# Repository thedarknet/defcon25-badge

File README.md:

# defcon25-badge
Badge Related items for defcon 25

Assembly instructions are located here:

https://dcdark.net/2017/badge/index.html

-----
Installation of IDE:
Follow the following instructions (step by step):  

http://gnuarmeclipse.github.io/install/

	Notes: on Window's have gotten both Mars and Luna to work
	on linux i've only gotten luna to work (on ubuntu 16.04 LTS)

Once eclipse is set up here's what the debug config needs to look like, notes the 2 -f openocd scripts that must be configured.

For 2017 development we are using this nucleo board, while it is not the exact MCU we plan to use it is close and the one we want to use does not have a dev kit.

http://www.st.com/content/st_com/en/products/evaluation-tools/product-evaluation-tools/mcu-eval-tools/stm32-mcu-eval-tools/stm32-mcu-nucleo/nucleo-f302r8.html

If you have the actual badge board you'll need debugging to look like this:

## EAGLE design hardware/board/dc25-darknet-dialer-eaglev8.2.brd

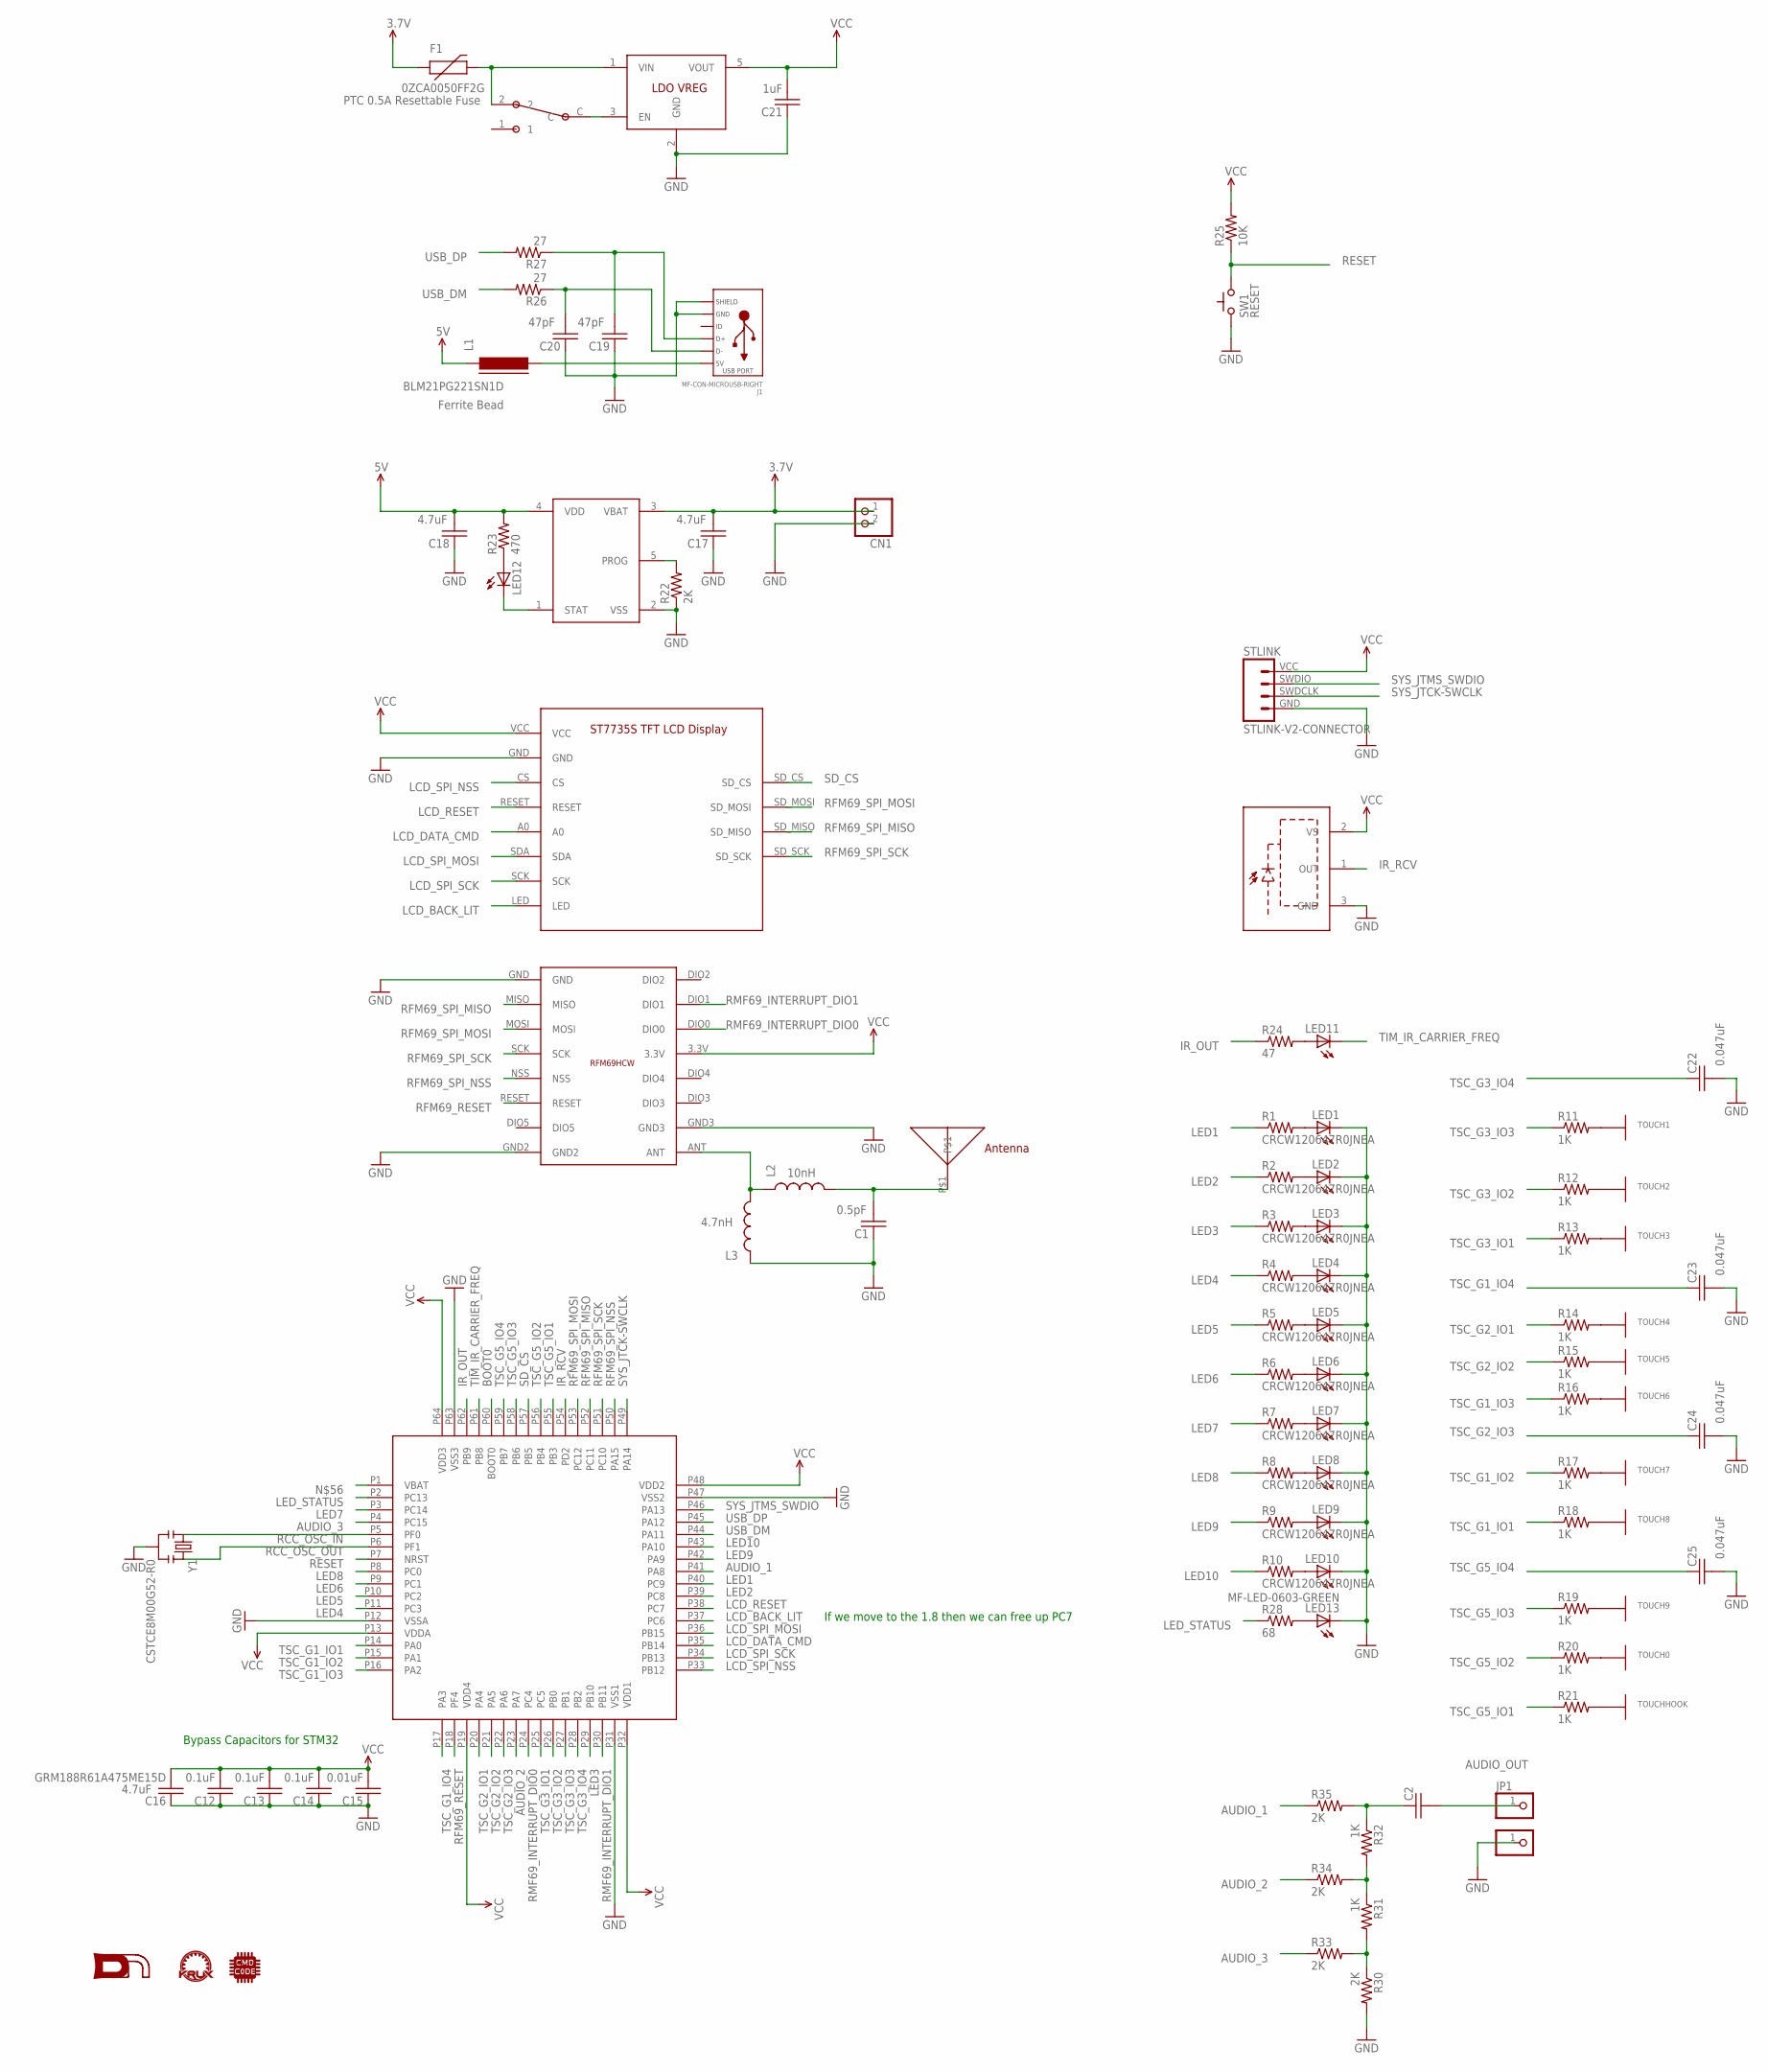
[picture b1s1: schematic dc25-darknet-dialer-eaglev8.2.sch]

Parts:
C1: 251R14S0R5BV4T; C0603
C2: GRM188C80G106ME47D; C0603
C12, C13, C14: 0.1uF; C0603
C15: 0.01uF; C0603
C16, C17, C18: GRM188R61A475ME15D; C0603
C19, C20: C0603C470J3GACTU; C0603
C21: 1uF; C0603
C22, C23, C24, C25: C0603C473J3RACAUTO; C0603
CN1: JST_2PIN-THM-RA; JST-PH-2-THM-RA
F1: 0ZCA0050FF2G; PTC-1206
J1: MF-CON-MICROUSB-RIGHT; MICROUSB-RIGHT
JP1, JP2: PINHD-1X1CB; 1X01-CLEANBIG
L1: BLM21PG221SN1D; FB603
L2: CI160808-10NJ; 0603
L3: CI160808-4N7D; 0603
LED1, LED2, LED3, LED4, LED5, LED6, LED7, LED8, LED9, LED10: LEDREVERSEMOUNT_NOPASTE; GULLWING_LED_NOPASTE
LED11: LED5MM
LED12, LED13: MF-LED-0603-GREEN; LED-0603
R1, R2, R3, R4, R5, R6, R7, R8, R9, R10: CRCW120647R0JNEA; 1206
R11, R12, R13, R14, R15, R16, R17, R18, R19, R20, R21, R31, R32: 1K; 0603-RES
R22, R30, R33, R34, R35: 2K; 0603-RES
R23: 470; 0603-RES
R24: 47; 0207/7
R25: 10K; 0603-RES
R26, R27: 27; 0603-RES
R28: 68; 0603-RES
STLINK: STLINK-V2-CONNECTOR; 1X04
SW1: RESET; TACTILE-2PIN-NARROW
TOUCH0: CAP_TOUCH0; CAP_TOUCH_PAD_0
TOUCH1: CAP_TOUCH1; CAP_TOUCH_PAD_1
TOUCH2: CAP_TOUCH2; CAP_TOUCH_PAD_2
TOUCH3: CAP_TOUCH3; CAP_TOUCH_PAD_3
TOUCH4: CAP_TOUCH4; CAP_TOUCH_PAD_4
TOUCH5: CAP_TOUCH5; CAP_TOUCH_PAD_5
TOUCH6: CAP_TOUCH6; CAP_TOUCH_PAD_6
TOUCH7: CAP_TOUCH7; CAP_TOUCH_PAD_7
TOUCH8: CAP_TOUCH8; CAP_TOUCH_PAD_8
TOUCH9: CAP_TOUCH9; CAP_TOUCH_PAD_9
TOUCHHOOK: CAP_TOUCHHOOK; CAP_TOUCH_PAD_HOOK
U1: BU33SD5WG-TR; SOT23-5
U2: MCP73831T-5ACI/OT; SOT23-5
U3: SOP22FLAT; IR-MODULE_FLAT
U$1: DN_LOGODC25; DARKNET_LOGO_DC25
U$2: STM32F302RBT6; LQFP64
U$11: SWITCH_SPDT; SPDT_SSAJ120100
U$12: KRUX_LOGO
U$15: RFM69HCWRFM69HCWSMDNOPASTE; 16PIN-PCB-SMD-NOPASTE
U$21: 0915AT43A0026E; CHIP_ANTENNA_1.8X8MM
U$22: ST7735S_LCD_MODULE; ST7735S_LCD_DISPLAY
U$23: CMD_C0DE_LOGO
Y1: CSTCE8M00G52-R0; RESONATOR-SMD

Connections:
ANT: L2.1, L3.2, U$15.ANT
AUDIO_1: R35.1, U$2.P41 (PA8)
AUDIO_2: R34.1, U$2.P23 (PA7)
AUDIO_3: R33.1, U$2.P4 (PC15)
AUDIO_OUT: C2.2, JP1.1
BOOT0: U$2.P60 (BOOT0)
GND: C1.1, C12.1, C13.1, C14.1, C15.1, C16.1, C17.1, C18.1, C19.1, C20.1, C21.1, C22.2, C23.2, C24.2, C25.2, CN1.2 (1), J1.5 (GND), J1.S1 (SLD), J1.S2 (SLD), J1.S3 (SLD), J1.S4 (SLD), J1.S5 (SLD), J1.S6 (SLD), JP2.1, L3.1, LED1.C, LED2.C, LED3.C, LED4.C, LED5.C, LED6.C, LED7.C, LED8.C, LED9.C, LED10.C, LED13.C, R22.1, R30.2, STLINK.GND, SW1.P$2 (C), U1.2 (GND), U2.2 (VSS), U3.3 (GND), U$2.P12 (VSSA), U$2.P31 (VSS1), U$2.P47 (VSS2), U$2.P63 (VSS3), U$15.GND, U$15.GND2, U$15.GND3, U$22.GND, Y1.2
IR_OUT: R24.1, U$2.P62 (PB9)
IR_RCV: U3.1 (OUT), U$2.P54 (PD2)
LCD_BACK_LIT: U$2.P37 (PC6), U$22.LED
LCD_DATA_CMD: U$2.P35 (PB14), U$22.A0
LCD_RESET: U$2.P38 (PC7), U$22.RESET
LCD_SPI_MOSI: U$2.P36 (PB15), U$22.SDA
LCD_SPI_NSS: U$2.P33 (PB12), U$22.CS
LCD_SPI_SCK: U$2.P34 (PB13), U$22.SCK
LED1: R1.1, U$2.P40 (PC9)
LED2: R2.1, U$2.P39 (PC8)
LED3: R3.1, U$2.P29 (PB10)
LED4: R4.1, U$2.P11 (PC3)
LED5: R5.1, U$2.P10 (PC2)
LED6: R6.1, U$2.P9 (PC1)
LED7: R7.1, U$2.P3 (PC14)
LED8: R8.1, U$2.P8 (PC0)
LED9: R9.1, U$2.P42 (PA9)
LED10: R10.1, U$2.P43 (PA10)
LED_STATUS: R28.1, U$2.P2 (PC13)
unnamed: R11.2, TOUCH1.PAD
unnamed: R12.2, TOUCH2.PAD
unnamed: R13.2, TOUCH3.PAD
unnamed: R14.2, TOUCH4.PAD
unnamed: R15.2, TOUCH5.PAD
unnamed: R16.2, TOUCH6.PAD
unnamed: R17.2, TOUCH7.PAD
unnamed: R18.2, TOUCH8.PAD
unnamed: R19.2, TOUCH9.PAD
unnamed: R20.2, TOUCH0.PAD
unnamed: R21.2, TOUCHHOOK.P$1
unnamed: LED1.A, R1.2
unnamed: LED2.A, R2.2
unnamed: LED3.A, R3.2
unnamed: LED4.A, R4.2
unnamed: LED5.A, R5.2
unnamed: LED6.A, R6.2
unnamed: LED7.A, R7.2
unnamed: LED8.A, R8.2
unnamed: LED9.A, R9.2
unnamed: LED10.A, R10.2
unnamed: R22.2, U2.5 (PROG)
unnamed: LED11.A, R24.2
unnamed: LED12.A, R23.1
unnamed: LED12.C, U2.1 (STAT)
unnamed: C19.2, J1.3 (D+), R27.1
unnamed: C20.2, J1.2 (D-), R26.1
unnamed: J1.1 (5V), L1.2
unnamed: LED13.A, R28.2
unnamed: F1.2, U1.1 (VIN), U$11.2
unnamed: C1.2, L2.2, U$21.P$1
unnamed: U1.3 (EN), U$11.C
unnamed: C2.1, R32.1, R35.2
unnamed: R31.1, R32.2, R34.2
unnamed: R30.1, R31.2, R33.2
RCC_OSC_IN: U$2.P5 (PF0), Y1.1
RCC_OSC_OUT: U$2.P6 (PF1), Y1.3
RESET: R25.1, SW1.P$1 (A), U$2.P7 (NRST)
RFM69_RESET: U$2.P18 (PF4), U$15.RESET
RFM69_SPI_MISO: U$2.P52 (PC11), U$15.MISO, U$22.SD_MISO
RFM69_SPI_MOSI: U$2.P53 (PC12), U$15.MOSI, U$22.SD_MOSI
RFM69_SPI_NSS: U$2.P50 (PA15), U$15.NSS
RFM69_SPI_SCK: U$2.P51 (PC10), U$15.SCK, U$22.SD_SCK
RMF69_INTERRUPT_DIO0: U$2.P24 (PC4), U$15.DIO0
RMF69_INTERRUPT_DIO1: U$2.P30 (PB11), U$15.DIO1
SD_CS: U$2.P57 (PB5), U$22.SD_CS
SYS_JTCK-SWCLK: STLINK.SWDCLK, U$2.P49 (PA14)
SYS_JTMS_SWDIO: STLINK.SWDIO, U$2.P46 (PA13)
TIM_IR_CARRIER_FREQ: LED11.K (C), U$2.P61 (PB8)
TSC_G1_IO1: R18.1, U$2.P14 (PA0)
TSC_G1_IO2: R17.1, U$2.P15 (PA1)
TSC_G1_IO3: R16.1, U$2.P16 (PA2)
TSC_G1_IO4: C23.1, U$2.P17 (PA3)
TSC_G2_IO1: R14.1, U$2.P20 (PA4)
TSC_G2_IO2: R15.1, U$2.P21 (PA5)
TSC_G2_IO3: C24.1, U$2.P22 (PA6)
TSC_G3_IO1: R13.1, U$2.P25 (PC5)
TSC_G3_IO2: R12.1, U$2.P26 (PB0)
TSC_G3_IO3: R11.1, U$2.P27 (PB1)
TSC_G3_IO4: C22.1, U$2.P28 (PB2)
TSC_G5_IO1: R21.1, U$2.P55 (PB3)
TSC_G5_IO2: R20.1, U$2.P56 (PB4)
TSC_G5_IO3: R19.1, U$2.P58 (PB6)
TSC_G5_IO4: C25.1, U$2.P59 (PB7)
USB_DM: R26.2, U$2.P44 (PA11)
USB_DP: R27.2, U$2.P45 (PA12)
VCC: C12.2, C13.2, C14.2, C15.2, C16.2, C21.2, R25.2, STLINK.VCC, U1.5 (VOUT), U3.2 (VS), U$2.P13 (VDDA), U$2.P19 (VDD4), U$2.P32 (VDD1), U$2.P48 (VDD2), U$2.P64 (VDD3), U$15.3.3V, U$22.VCC
VCC0: C18.2, L1.1, R23.2, U2.4 (VDD)
VCC1: C17.2, CN1.1 (2), F1.1, U2.3 (VBAT)

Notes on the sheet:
If we move to the 1.8 then we can free up PC7
Bypass Capacitors for STM32
0.5pF
4.7uF
47pF
0.047uF
PTC 0.5A Resettable Fuse
Ferrite Bead
10nH
4.7nH

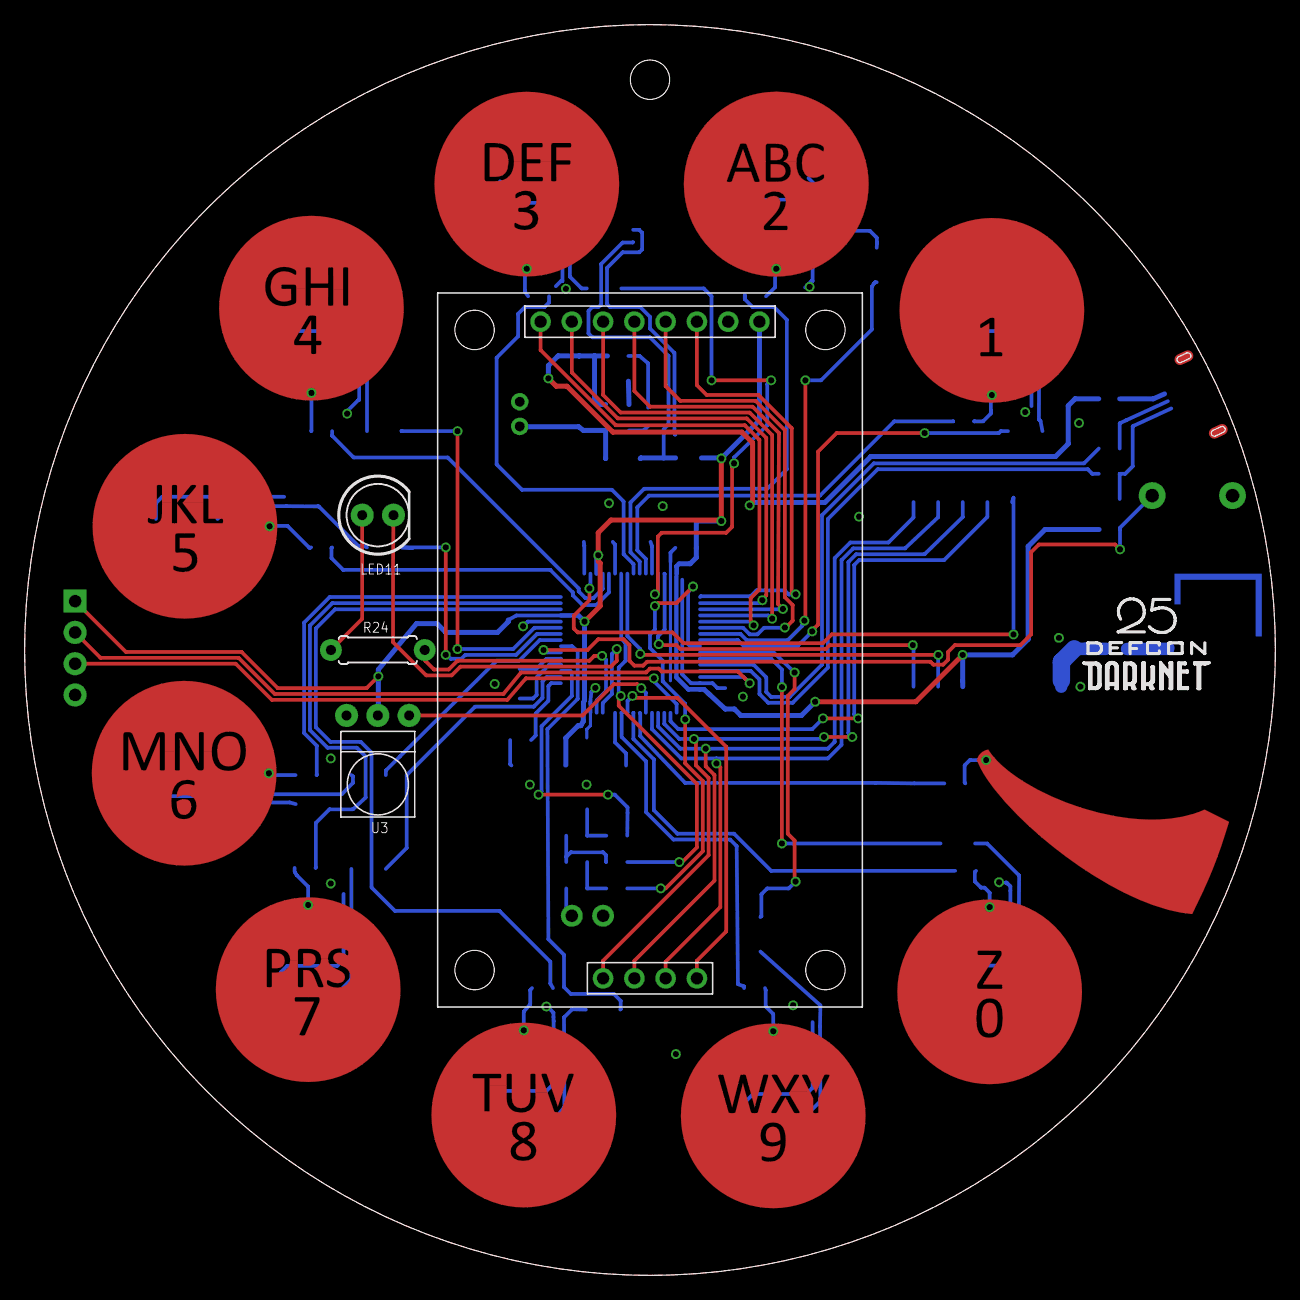
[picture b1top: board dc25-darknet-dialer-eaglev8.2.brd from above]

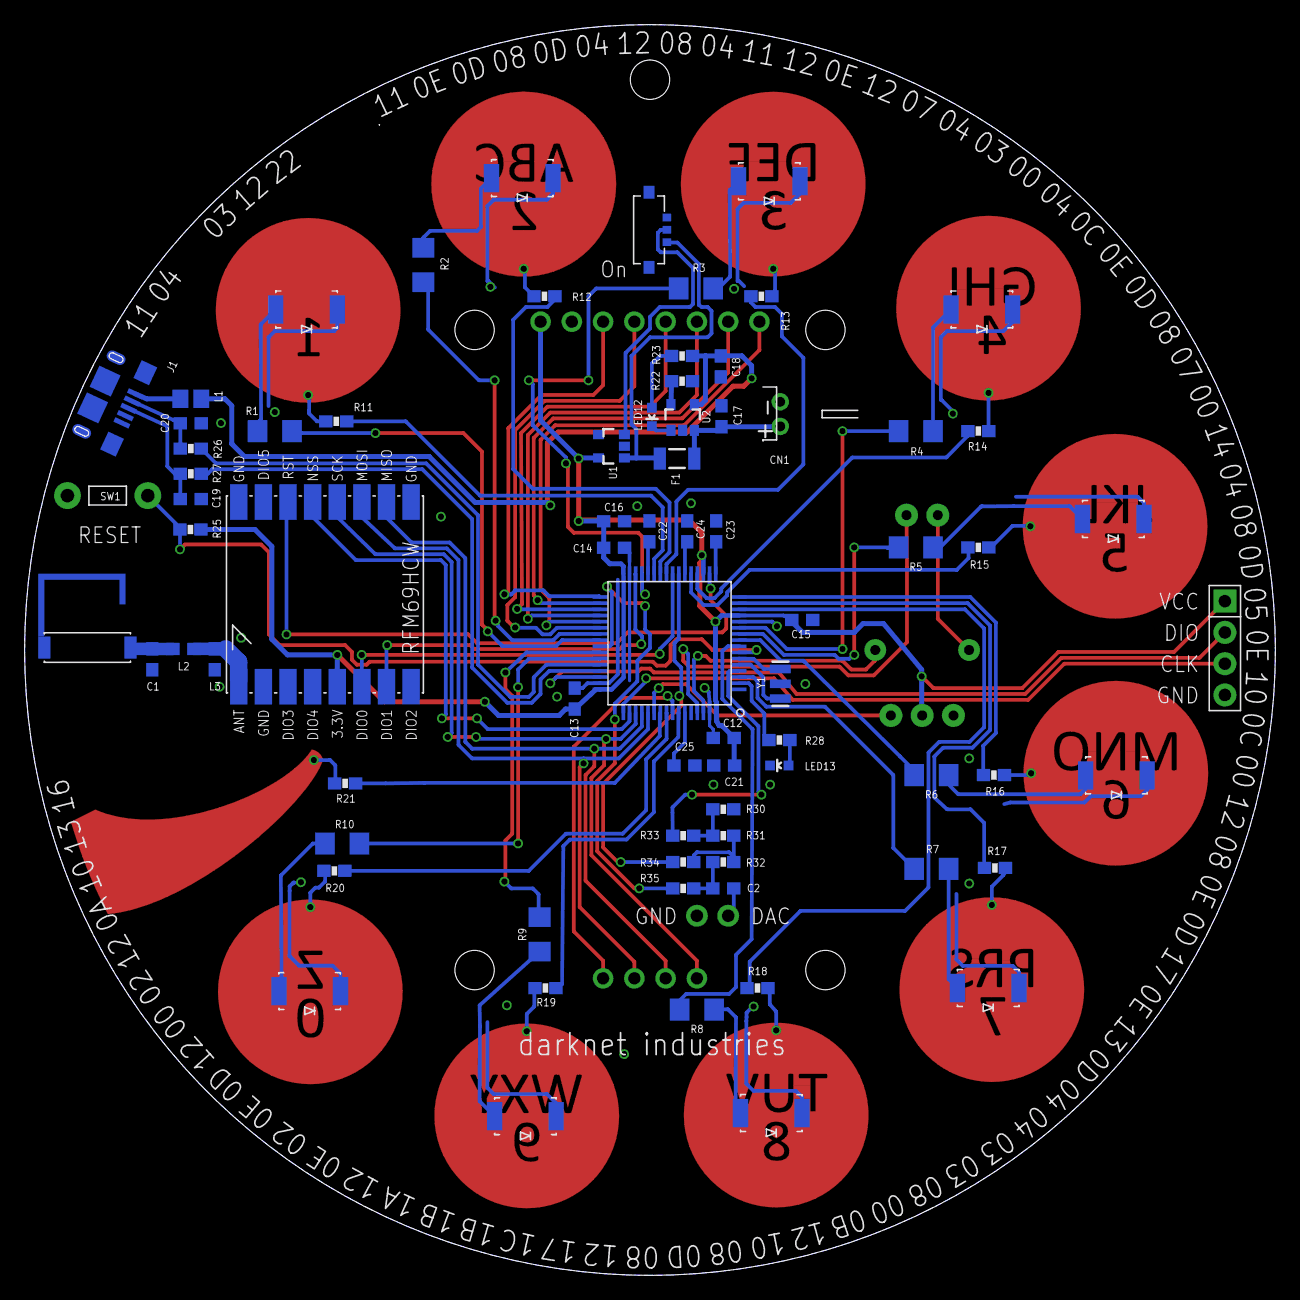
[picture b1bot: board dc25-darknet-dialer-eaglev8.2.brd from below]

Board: 2 copper layers, 101.6 x 101.6 mm, 96 parts (78 on the bottom side), 94 nets.

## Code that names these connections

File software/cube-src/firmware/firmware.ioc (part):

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Mcu.Name=STM32F302R(B-C)Tx
Mcu.Package=LQFP64
Mcu.UserName=STM32F302RBTx
PA0.Mode=G1_IO1-Channel
PA0.Signal=TSC_G1_IO1
PA1.Mode=G1_IO2-Channel
PA1.Signal=TSC_G1_IO2
PA10.GPIOParameters=GPIO_Label
PA10.GPIO_Label=LED10
PA10.Signal=GPIO_Output
PA11.Mode=Device
PA11.Signal=USB_DM
PA12.Mode=Device
PA12.Signal=USB_DP
PA13.Mode=Serial_Wire
PA13.Signal=SYS_JTMS-SWDIO
PA14.Mode=Serial_Wire
PA14.Signal=SYS_JTCK-SWCLK
PA15.GPIOParameters=GPIO_Label
PA15.GPIO_Label=RADIO_SPI3_NSS
PA15.Mode=NSS_Signal_Hard_Output
PA15.Signal=SPI3_NSS
PA2.Mode=G1_IO3-Channel
PA2.Signal=TSC_G1_IO3
PA3.Mode=G1_IO4-Sampling
PA3.Signal=TSC_G1_IO4
PA4.Mode=G2_IO1-Channel
PA4.Signal=TSC_G2_IO1
PA5.Mode=G2_IO2-Channel
PA5.Signal=TSC_G2_IO2
PA6.Mode=G2_IO3-Sampling
PA6.Signal=TSC_G2_IO3
PA7.GPIOParameters=GPIO_Label
PA7.GPIO_Label=AUDIO_2
PA7.Signal=GPIO_Output
PA8.GPIOParameters=GPIO_Label
PA8.GPIO_Label=AUDIO1
PA8.Signal=GPIO_Output
PA9.GPIOParameters=GPIO_Label
PA9.GPIO_Label=LED9
PA9.Signal=GPIO_Output
PB0.Mode=G3_IO2-Channel
PB0.Signal=TSC_G3_IO2
PB1.Mode=G3_IO3-Channel
PB1.Signal=TSC_G3_IO3
PB10.GPIOParameters=GPIO_Label
PB10.GPIO_Label=LED3
PB10.Signal=GPIO_Output
PB11.GPIOParameters=GPIO_Label
PB11.GPIO_Label=RADIO_INTERRUPT_DIO1_EXTI11
PB11.Signal=GPXTI11
PB12.GPIOParameters=GPIO_Label
PB12.GPIO_Label=LCD_CS
PB12.Signal=GPIO_Output
PB13.GPIOParameters=GPIO_Label
PB13.GPIO_Label=LCD_SPI2_SCK
PB13.Mode=Simplex_Bidirectional_Master
PB13.Signal=SPI2_SCK
PB14.GPIOParameters=GPIO_Label
PB14.GPIO_Label=LCD_DATA_CMD
PB14.Signal=GPIO_Output
PB15.GPIOParameters=GPIO_Label
PB15.GPIO_Label=LCD_SPI2_MOSI
PB15.Mode=Simplex_Bidirectional_Master
PB15.Signal=SPI2_MOSI
PB2.Mode=G3_IO4-Sampling
PB2.Signal=TSC_G3_IO4
PB3.Mode=G5_IO1-Channel
PB3.Signal=TSC_G5_IO1
PB4.Mode=G5_IO2-Channel
PB4.Signal=TSC_G5_IO2
PB5.GPIOParameters=GPIO_Label
PB5.GPIO_Label=SD_CARD_CS
PB5.Signal=GPIO_Output
PB6.Mode=G5_IO3-Channel
PB6.Signal=TSC_G5_IO3
PB7.Mode=G5_IO4-Sampling
PB7.Signal=TSC_G5_IO4
PB8.GPIOParameters=GPIO_Label
PB8.GPIO_Label=TIM_IR_CARRIER_FREQ
PB8.Signal=S_TIM16_CH1
PB9.GPIOParameters=GPIO_Speed,GPIO_Label
PB9.GPIO_Label=IR_TX
PB9.GPIO_Speed=GPIO_SPEED_FREQ_HIGH
PB9.Signal=GPIO_Output
PC0.GPIOParameters=GPIO_Label
PC0.GPIO_Label=LED8
PC0.Signal=GPIO_Output
PC1.GPIOParameters=GPIO_Label
PC1.GPIO_Label=LED6
PC1.Signal=GPIO_Output
PC10.GPIOParameters=GPIO_Label
PC10.GPIO_Label=RADIO_SPI3_SCK
PC10.Mode=Full_Duplex_Master
PC10.Signal=SPI3_SCK
PC11.GPIOParameters=GPIO_Label
PC11.GPIO_Label=RADIO_SPI3_MISO
PC11.Mode=Full_Duplex_Master
PC11.Signal=SPI3_MISO
PC12.GPIOParameters=GPIO_Label
PC12.GPIO_Label=RADIO_SPI3_MOSI
PC12.Mode=Full_Duplex_Master
PC12.Signal=SPI3_MOSI
PC13.GPIOParameters=GPIO_Label
PC13.GPIO_Label=LED_STATUS
PC13.Signal=GPIO_Output
PC14-OSC32_IN.GPIOParameters=GPIO_Label
PC14-OSC32_IN.GPIO_Label=LED7
PC14-OSC32_IN.Signal=GPIO_Output
PC15-OSC32_OUT.GPIOParameters=GPIO_Label
PC15-OSC32_OUT.GPIO_Label=AUDIO3
PC15-OSC32_OUT.Signal=GPIO_Output
PC2.GPIOParameters=GPIO_Label
PC2.GPIO_Label=LED5
PC2.Signal=GPIO_Output
PC3.GPIOParameters=GPIO_Label
PC3.GPIO_Label=LED4
PC3.Signal=GPIO_Output
PC4.GPIOParameters=GPIO_Label
PC4.GPIO_Label=RADIO_INTERRUPT_DIO0_EXTI4
PC4.Signal=GPXTI4
PC5.Mode=G3_IO1-Channel
PC5.Signal=TSC_G3_IO1
PC6.GPIOParameters=GPIO_Label
PC6.GPIO_Label=LCD_BACK_LIT
PC6.Signal=GPIO_Output
PC7.GPIOParameters=GPIO_Label
PC7.GPIO_Label=LCD_RESET
PC7.Signal=GPIO_Output
PC8.GPIOParameters=GPIO_Label
PC8.GPIO_Label=LED2
PC8.Signal=GPIO_Output
PC9.GPIOParameters=GPIO_Label
PC9.GPIO_Label=LED1
PC9.Signal=GPIO_Output
PD2.GPIOParameters=GPIO_Label,GPIO_ModeDefaultEXTI
PD2.GPIO_Label=IR_RCV
PD2.GPIO_ModeDefaultEXTI=GPIO_MODE_IT_RISING_FALLING
PD2.Signal=GPXTI2
PF0-OSC_IN.Mode=HSE-External-Oscillator
PF0-OSC_IN.Signal=RCC_OSC_IN
PF1-OSC_OUT.Mode=HSE-External-Oscillator
PF1-OSC_OUT.Signal=RCC_OSC_OUT
PF4.GPIOParameters=GPIO_Label
PF4.GPIO_Label=RFM69_RESET
PF4.Signal=GPIO_Output
RCC.HSEPLLFreq_Value=8000000
RCC.HSE_VALUE=8000000
RCC.SYSCLKFreq_VALUE=72000000
RCC.SYSCLKSourceVirtual=RCC_SYSCLKSOURCE_PLLCLK
board=firmware

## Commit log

2016-12-27 adding pdf for hardware components.
2016-12-27 adding development board - dev board only has 64K flash rather than 128K
2016-12-27 chip we are planning on using is stm32f3CB not RB
2016-12-27 yes we are using the rb as that rb is the 64 pin version
2016-12-27 adding example code
2016-12-28 adding stm32cubemx file
2016-12-28 cube-gen is where stm32cubemx generates the sw project, then we use cubemximporter to re-jigger the files into a eclipse project under firmware.
2016-12-28 notes
2017-01-04 Added Eagle PCB files
2017-01-04 added docs on the Li-Ion/Li-Po charge controller
2017-01-04 Updated board to include values for bypass caps
2017-01-18 initial (what could be a test project) project for 2017
2017-01-22 inital badge file starts
2017-01-25 Routing and layout progress
2017-01-25 updated conf
2017-01-26 Updated design
2017-02-06 Added library file
2017-02-07 Added power and IR
2017-02-07 Updated power, wired IR
2017-02-08 Connected LEDs
2017-02-08 Added resonator
2017-02-08 DRC fixes
2017-02-09 Additional details on power, added fuse and prep for 3.3v LDO
2017-02-12 1.8 lcd string has very very very basic functionality
2017-02-12 closer
2017-02-12 Updated with additional instructions
2017-02-12 updated png with debug for nucleo fixed file encoding for display_device
2017-02-13 display now works, still need some code clean up and a pass to ensure we are handling the CS and data/cmd pins correctly
2017-02-14 more documentation and clarity between the 1.8" displays and the 1.44 setpixelformat and set memory access control MUST be set before the initialization for teh ST7735
2017-02-14 remove currupt file
2017-03-04 adding eagle version 8 files to ensure krux can open
2017-03-05 added stlink connector to lbr moved radio spi from spi1 to spi3 to free up pins for touch sensening
2017-03-08 moved parts onto board, but not in correct location yet
2017-03-12 updates to only have 1 pin for IR timer added todo list
2017-03-12 added new part to library: SD_CARD_HEADER diff of todo.txt shows what else was completed on this check in. adding another doc on cap sense and updated stm32cube file
2017-03-14 Updated parts library
2017-03-14 Cleanup and update of schematic, added voltage regulator
2017-03-17 software control of backlight, new ioc file closer to what final will be
2017-03-17 moving current firmware to a test directory so we can use it for 1 off tests
2017-03-17 updated name so it isn't confusing with actual firmware
2017-03-19 new project does not compile yet
2017-03-19 Updated display module, added antenna design
2017-03-19 Changed status LED for board debugging
2017-03-19 now new project compiles
2017-03-19 updated language settings (should this file even get checked in?)
2017-03-19 working display again
2017-03-19 more fonts work
2017-03-20 Finished routing
2017-03-21 Changed orientation of IR reciver
2017-03-21 Updated silk screen parts indicators
2017-03-23 Updated parts for upload to MacroFab
2017-03-27 basics of menu-ing system working (ported from last years badge)
2017-04-11 3d engine coded need to test
2017-04-17 Changed USB connector to Macrofab eagle library
2017-04-17 Added on/off switch
2017-04-24 Minor tweaks
2017-04-24 added 3-bit DAC circuit
2017-04-24 Added audio out pads
2017-04-25 more working 3d renderer
2017-04-27 added code to test leds
2017-04-30 fixed compiler bug
2017-04-30 updated pin definition to support Audio pins
2017-04-30 updated linker script to use all memory (as the dev board was smaller in flash and ram)
2017-04-30 basic communication with Radio appears to work
2017-05-01 touchpad keyboard hardware test is working
2017-05-01 start of code to test IR
2017-05-01 closer to IR working
2017-05-02 more menus working
2017-05-03 more fixes
2017-05-03 Updated switch hook, and removed solder paste for kit parts
2017-05-05 game of life actually works correctly but only 32 columns...
2017-05-05 BadgeGen Source from last year added
2017-05-05 flash shit is now right
2017-05-07 IR Ready to test
2017-05-07 closer to a working IR IRQ's where configured wrong, clock was configured wrong
2017-05-08 Updated silk screen on parts library
2017-05-08 added puzzle silk screen
2017-05-08 IR Receive works! TX not so much
2017-05-09 Fixed puzzle silk screen, minor ground fill tweaks
2017-05-09 added badge debugging info
2017-05-09 Moved the radio board over a little to give more room to solder.
2017-05-10 moved resistor silk screen
2017-05-14 fixed a bunch of small visual bugs
2017-05-14 drawRec implemented
2017-05-15 fixed a number of small display bugs
2017-05-23 updated schematic to populate audio
2017-05-23 Helps if one saves
2017-05-23 initial check in
2017-05-24 removed dead code,
2017-05-24 Updated library for new logo
2017-05-24 added revision 3 of the board
2017-05-24 Fixed spacing around switch hook
2017-06-02 new framebuffer no buffer class working
2017-06-02 keyboard test now prints in the right location
2017-06-02 fixed release build of firmware
2017-06-02 2d fast rendering working....just need to build color look up table.
2017-06-02 fixed a bug with saving screen saver time colors render right with new optimzed renderer
2017-06-02 small bug fixes
2017-06-04 clean up
2017-06-18 dialer leds working
2017-06-18 init sequence now working
2017-06-18 more 3d work
2017-06-18 small fix to compiler warning
2017-06-18 Now led under pad selection lights up.
2017-06-18 Now since we can render the screen faster I'm removing the conditional screen renders so that the scrolling works again.
2017-06-21 set 5 to up and 6 to down
2017-06-30 72 Mhz rather than 48
2017-07-03 rendering - probably need to move to indexed - strips for triangles
2017-07-05 faster sin/cos lookup
2017-07-09 added images
2017-07-12 added krux's number
2017-07-13 notes for dialer moving setting sector
2017-07-13 fixed a few smaller bugs
2017-07-16 basic communication to RFM69 working
2017-07-16 threading added
2017-07-16 ready to test
2017-07-17 turning off USB for now
2017-07-17 removing settings from git
2017-07-17 all 3d imporvements
2017-07-17 removing usb and fixes to draw image
2017-07-17 fixed line of code that excited compiler bug turned off boot image when debugging to save space
2017-07-17 dialer nearly done
2017-07-17 closer on dialer
2017-07-18 Badge Dialer - 'done'
2017-07-19 adding python programmer scripts from dc24
2017-07-22 trips now work
2017-07-22 fixed bug with slow rendering on set agent name screen
2017-07-22 fixed clear screen bug on entering 3d we now start on the menu screen again
2017-07-23 gateway
2017-07-23 basic communication from badge working
2017-07-24 check in alpha firmware
2017-07-24 updated flash python to use correct 2017 value
2017-07-28 removed alpha flag encoded dialer numbers added blinky to screen saver
2017-07-28 fixed but with display of long message
2017-07-28 listen a little faster
2017-07-30 fixed bug with dialer
2017-08-08 Update README.md
    Added link to the assembly instructions
2017-08-31 Added Bill of Materials
2018-02-26 scale version
2018-03-09 fixed the darknet message not being received if screen saver or 3d mode is running
2018-03-09 upped version number so we know which has the latest at scale16x

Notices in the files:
parts and their libraries:
SparkFun: Licensing: CC v3.0 Share-Alike You are welcome to use this library for commercial purposes.
